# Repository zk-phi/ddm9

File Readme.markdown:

# DDM9

名刺サイズの９キーパッドです。名刺としてもワンチャン使えるものを想定してデザインしました。

販売予定はいまのところありません。 meishi 交換しましょう。

## イメージ

表

裏

実装例

## 免責事項

組み立て中・使用中のトラブルについては保証できません。 DIY の精神でチャレンジしてみてください。

## 工具

最低限必要なもの：

- ハンダ
  - 鉛入り (鉛フリー以外) のものの方が溶けやすくて簡単です
  - 鉛を取り込むと体に悪いので、作業後は机の清掃や手洗いをしてください

- ハンダ小手
  - そこまで高くないので、温度調整機能があるものを買った方が断然簡単です (FX-600 がおすすめ)
  - 特に LED を付ける場合は熱で壊れてしまうので温度調整が必須です

- ハンダ小手台
  - アツアツのはんだごてが転がってくると熱いので、安定感のある (できれば専用の) 台が必要です

- 小手先クリーナー (タワシみたいなやつでもスポンジみたいなやつでも ok)

あったほうがよいもの：

- ハンダ吸い取り線 または ハンダ吸い取り機
  - 失敗した時のリカバリに必須です

- マルチテスター
  - ちゃんと繋がっているかどうかさえ判定できればいいので、怪しい安物で全然 ok です

## 部品表

基板の他に：

- コンスルー付き Pro Micro x1
  - 遊舎工房さんで購入する場合
    - https://yushakobo.jp/shop/promicro-spring-pinheader/
  - TALP KEYBOARD さんで購入する場合
    - https://talpkeyboard.stores.jp/items/5b24504ba6e6ee7ec60063e3
    - https://talpkeyboard.stores.jp/items/5e056626d790db16e2889233

- Kailh Choc スイッチ x9 (V2 でない)
  - https://yushakobo.jp/shop/pg1350/

- SK6812mini LED x9 (オプション)
  - 遊舎工房さんで購入する場合
    - https://yushakobo.jp/shop/sk6812mini-35/
  - 秋月電子さんで購入する場合
    - http://akizukidenshi.com/catalog/g/gI-15477/

- 完成した基板をいい感じに設置する手段

が必要です。

### 基板設置のアイデア

一番簡単なのは、基板の隅に大きめのプラ足・ゴム足などを貼り付けて設置です。このとき高さは 6mm 以上稼ぐようにしてください (部品が机に当たります)。万一部品が机に当たってしまってもショートしたりすることがないよう、金属製の机などは避けて作業してください。

次におそらく簡単なのは、名刺サイズの適当な板の四隅に 2mm 程度の穴を開けて、 M2 ネジ・高ナットを使って基板と連結することで底板になってもらう方法です (基板の四隅の穴はそのために開けてあります)。もしこの名刺基板を２枚ゲットすることができたら、片方を底板にしてしまえばネジ締めだけで完成するので楽チンです。

工作に慣れている方は、ケースを自作するのもアリです。

## 組立て
### Pro Micro にファームを焼く

https://github.com/zk-phi/keyboard-buildguide-common/blob/master/firmware.markdown

[こちら](https://github.com/zk-phi/qmk_firmware) に私の使っているキーマップがアップロードされています。

```
make handwired/ddm9:default:avrdude
```

### Pro Micro にコンスルーをつける

ProMicro を基板に連結するためのコンスルーを実装します。

温度調整機能のある小手を持っている場合は、 320 度程度が使いやすいです。

https://github.com/zk-phi/keyboard-buildguide-common/blob/master/conthrough.markdown

このキーボードでは ProMicro を「部品面が内側になるように」使用します。

### LED をつける (オプション)

LED の半田付けは難しいので、自信がない場合はスキップ推奨です。

また、熱で壊れてしまうので温度調整機能付きの半田ごてが必須です。

https://github.com/zk-phi/keyboard-buildguide-common/blob/master/neopixel.markdown

1, 2, ... 9 の順で直列に繋がっているので、この順番で実装してください。

### キースイッチをつける

キースイッチを 9 個取り付けます。順番などは気にしなくて ok です。

LED を取り付けていた場合は、ハンダ小手の温度を 320 度程度に戻して大丈夫です。アツアツの小手を LED にジューしてせっかくつけた LED を破壊しないようにだけ注意してください。

X の目印があるピンは Pro Micro の USB コネクタなどにぶつかってしまうので、基板の表面ギリギリでカットしてから、少なめのハンダで (山盛りにしないように) なるべく平らになるようにつけてあげてください。切った足は飛んで行ってしまうことがあり危険なので、指で押さえながら切りましょう。

Pro Micro を差し込んでみて、キー入力ができれば ok です。

### 活用する

適当な方法で基板を設置してあげてください。

キーマップは `qmk_firmware/keyboards/handwired/ddm9/keymaps/default/keymap.c` に定義されています。

このファイルを修正し、再度 Pro Micro にファームウェアを書き込むことで、好きなキーを入力することができます。

よく使うアプリケーションのショートカット (Web 会議のミュートなど) を設定しておくとちょっと便利です。

使用できるキーの一覧は [このあたり](https://docs.qmk.fm/#/ja/keycodes) を参照してください。

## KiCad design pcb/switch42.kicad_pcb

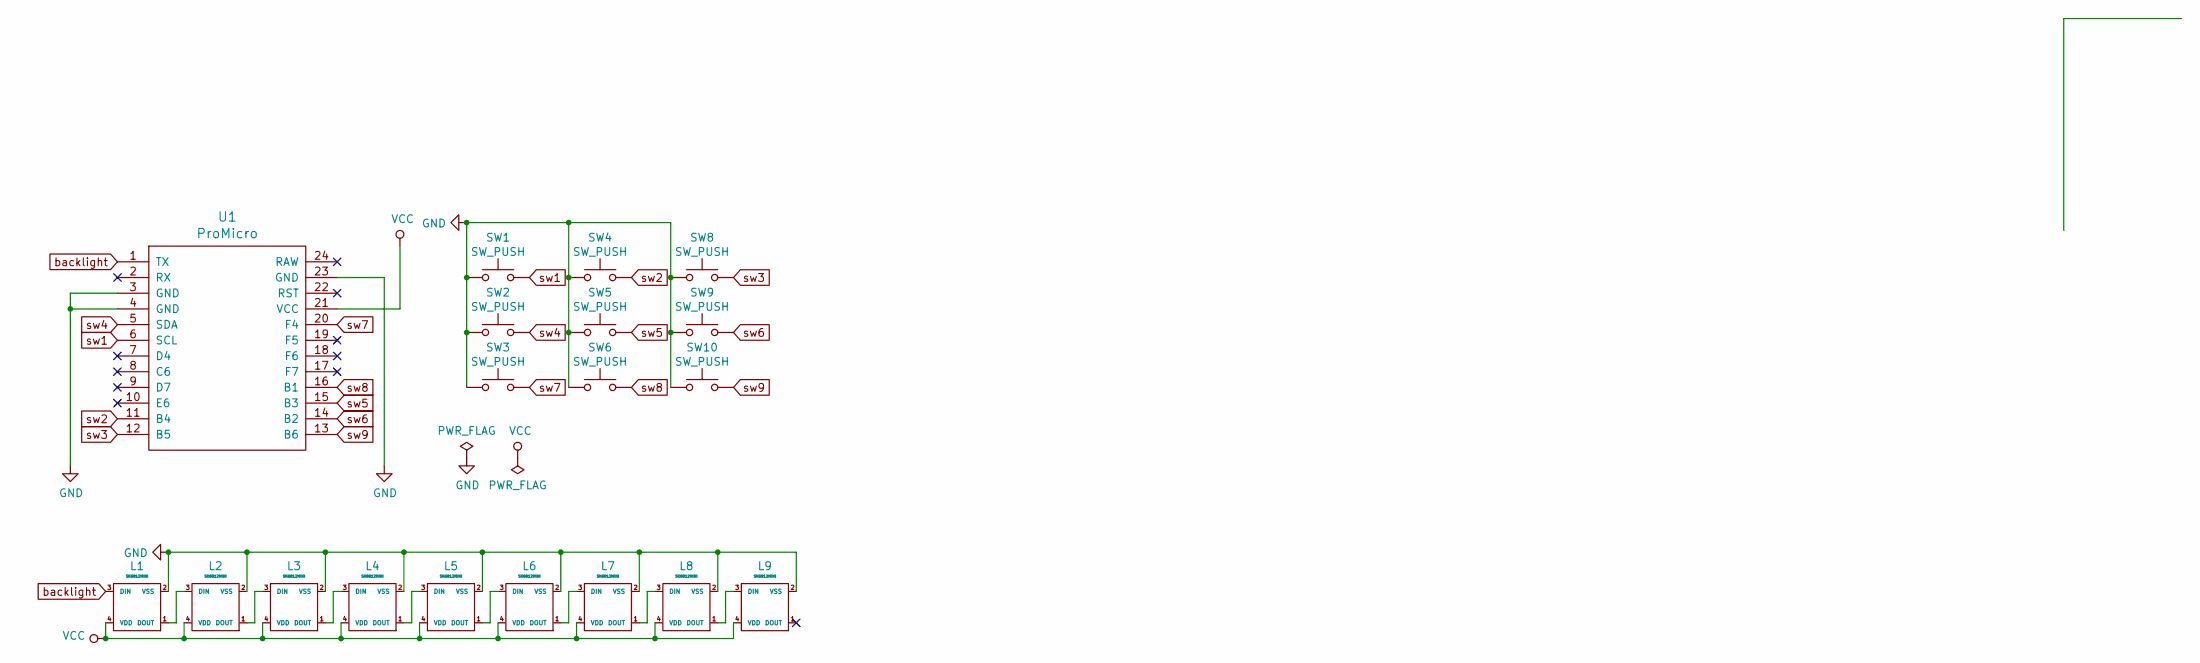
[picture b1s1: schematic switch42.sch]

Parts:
L1, L2, L3, L4, L5, L6, L7, L8, L9: SK6812MINI; SK6812MINI-irreversible
SW1, SW2, SW3, SW4, SW5, SW6, SW8, SW9, SW10: SW_PUSH; Choc_1.00u-narrow-irreversible
U1: ProMicro; ProMicro_Reversed_Conthrough-irreversible

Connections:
GND: L1.2 (VSS), L2.2 (VSS), L3.2 (VSS), L4.2 (VSS), L5.2 (VSS), L6.2 (VSS), L7.2 (VSS), L8.2 (VSS), L9.2 (VSS), SW1.1, SW2.1, SW3.1, SW4.1, SW5.1, SW6.1, SW8.1, SW9.1, SW10.1, U1.3 (GND), U1.4 (GND), U1.23 (GND)
unnamed: L1.1 (DOUT), L2.3 (DIN)
unnamed: L2.1 (DOUT), L3.3 (DIN)
unnamed: L3.1 (DOUT), L4.3 (DIN)
unnamed: L4.1 (DOUT), L5.3 (DIN)
unnamed: L5.1 (DOUT), L6.3 (DIN)
unnamed: L6.1 (DOUT), L7.3 (DIN)
unnamed: L7.1 (DOUT), L8.3 (DIN)
unnamed: L8.1 (DOUT), L9.3 (DIN)
VCC: L1.4 (VDD), L2.4 (VDD), L3.4 (VDD), L4.4 (VDD), L5.4 (VDD), L6.4 (VDD), L7.4 (VDD), L8.4 (VDD), L9.4 (VDD), U1.21 (VCC)
backlight: L1.3 (DIN), U1.1 (TX)
sw1: SW1.2, U1.6 (SCL)
sw2: SW4.2, U1.11 (B4)
sw3: SW8.2, U1.12 (B5)
sw4: SW2.2, U1.5 (SDA)
sw5: SW5.2, U1.15 (B3)
sw6: SW9.2, U1.14 (B2)
sw7: SW3.2, U1.20 (F4)
sw8: SW6.2, U1.16 (B1)
sw9: SW10.2, U1.13 (B6)

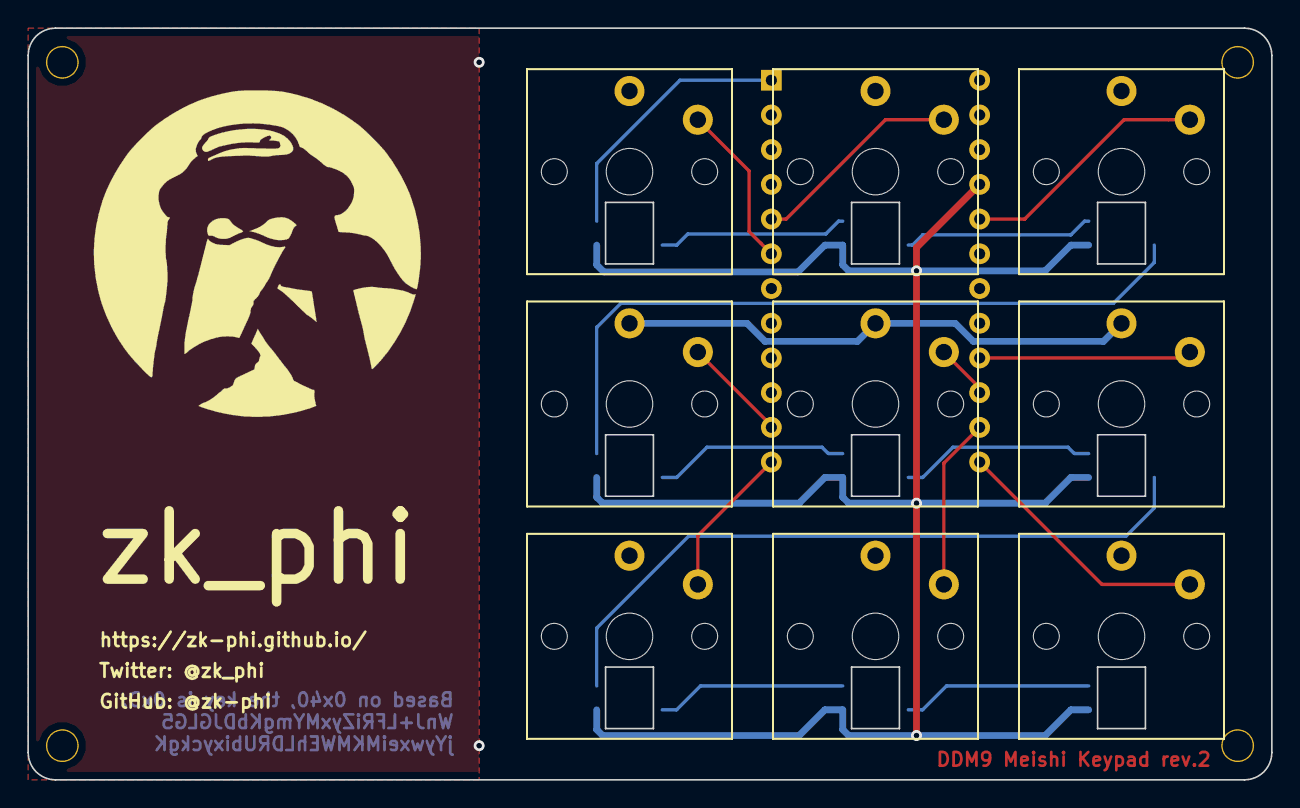
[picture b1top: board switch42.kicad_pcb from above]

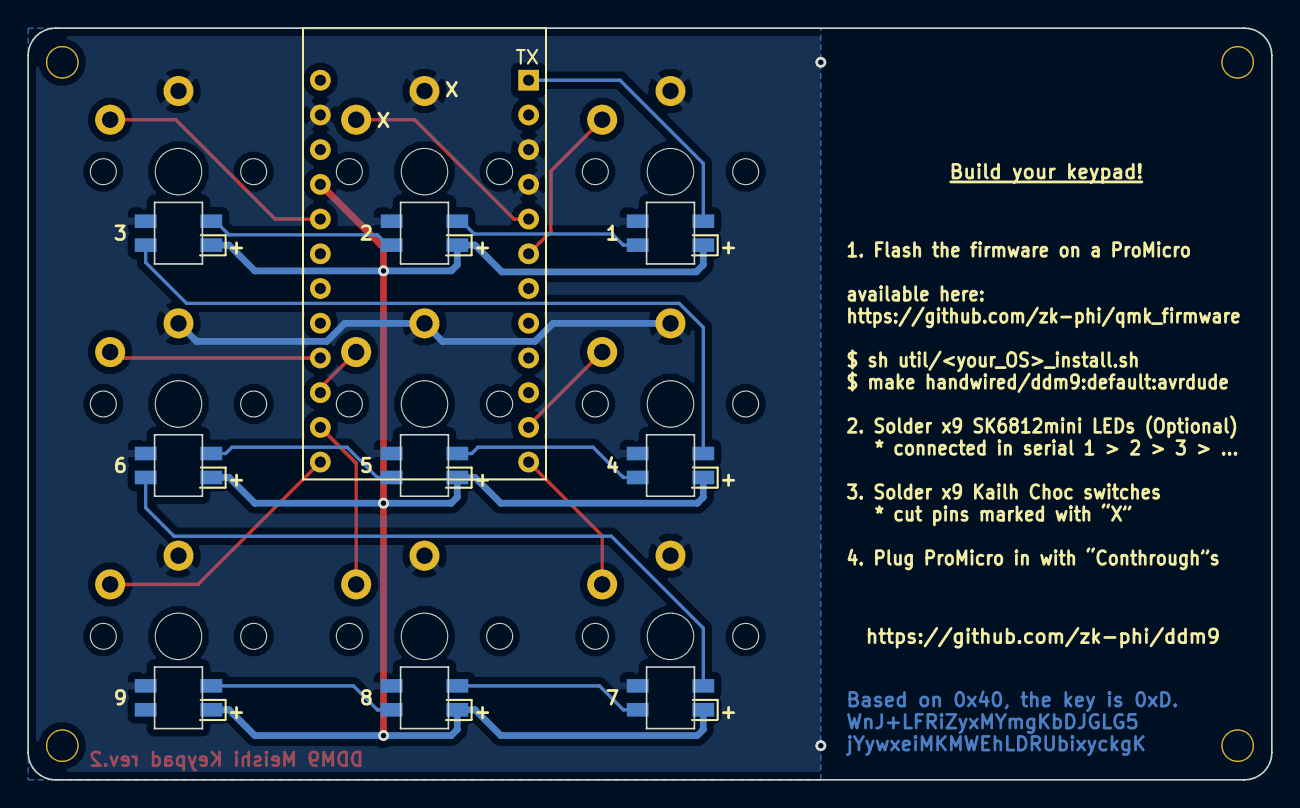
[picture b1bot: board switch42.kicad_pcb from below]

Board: 2 copper layers, 91.0 x 55.0 mm, 23 parts (10 on the bottom side), 20 nets.

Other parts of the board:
Ref**: Val**; M2_SCREW_HOLE_Plated
Ref**#2, Ref**#3, Ref**#4: Val**; M2_SCREW_HOLE_Plated

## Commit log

2020-07-19 Fix markdown syntax
2020-07-19 Move meishi contents slightly upward
2020-07-19 Get screw holes plated
2020-08-20 Update challenge
2020-08-20 Update buildguide
2020-08-20 Update texts
2020-08-20 Update images
2020-08-20 Fix texts
2020-08-26 Replace footprints
2020-08-26 Rename rename.sh
